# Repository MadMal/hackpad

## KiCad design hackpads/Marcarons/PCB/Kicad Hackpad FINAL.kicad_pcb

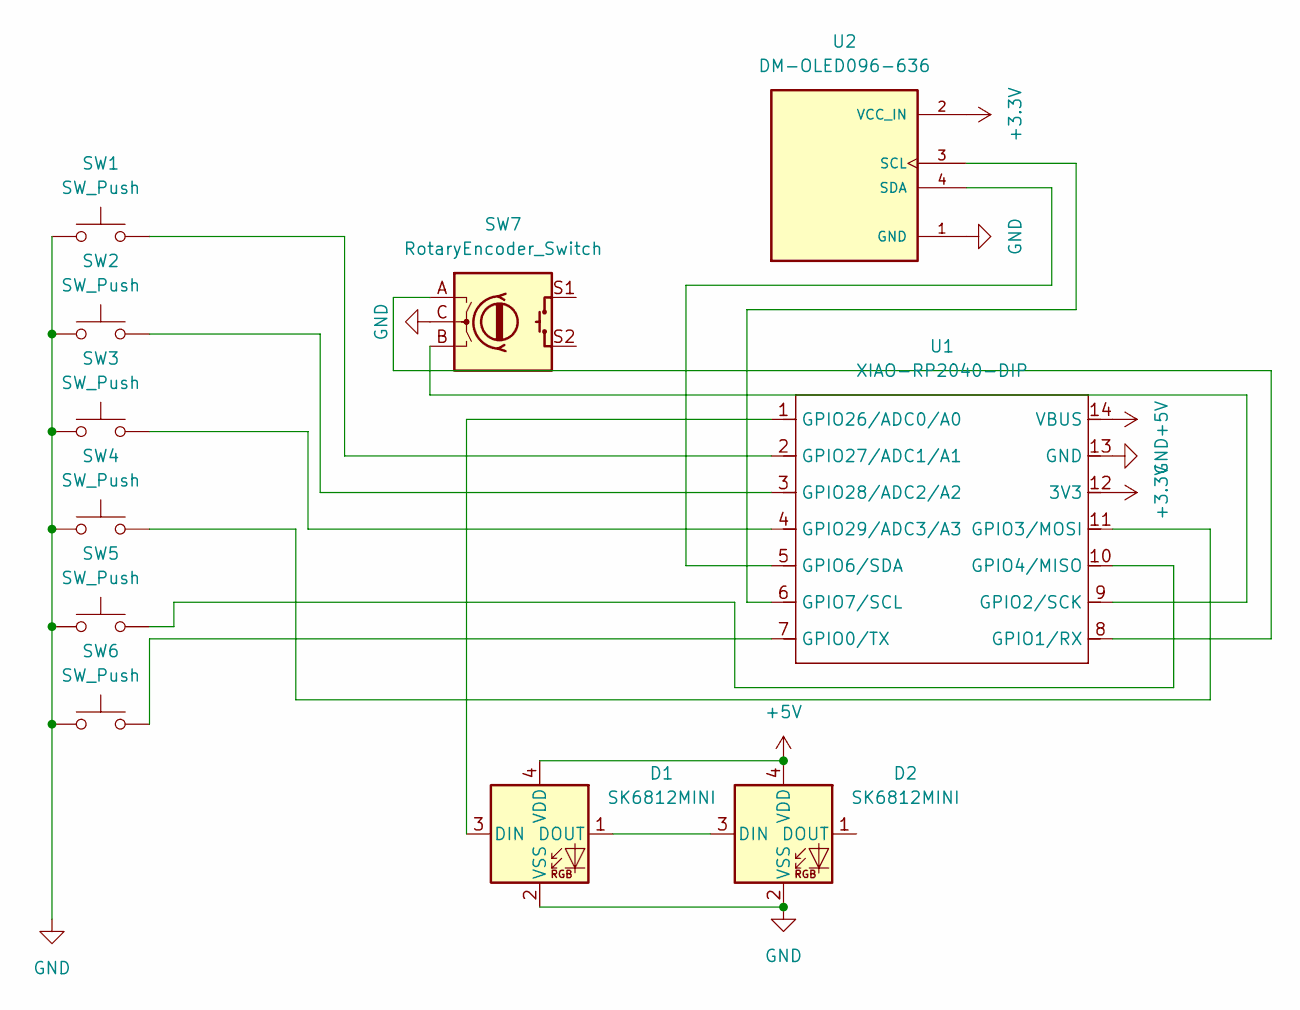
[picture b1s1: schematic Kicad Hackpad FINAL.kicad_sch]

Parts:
D1, D2: SK6812MINI; LED_SK6812MINI_PLCC4_3.5x3.5mm_P1.75mm
SW1, SW2, SW3, SW4, SW5, SW6: SW_Push; SW_Cherry_MX_1.00u_PCB
SW7: RotaryEncoder_Switch; RotaryEncoder_Alps_EC11E-Switch_Vertical_H20mm
U1: XIAO-RP2040-DIP
U2: DM-OLED096-636; SSD1306-0.91-OLED-4pin-128x32; PARTREV 2018-09-10

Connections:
+3.3V: U1.12 (3V3), U2.2 (VCC_IN)
+5V: D1.4 (VDD), D2.4 (VDD), U1.14 (VBUS)
GND: D1.2 (VSS), D2.2 (VSS), SW1.1, SW2.1, SW3.1, SW4.1, SW5.1, SW6.1, SW7.C, U1.13 (GND), U2.1 (GND)
unnamed: D1.3 (DIN), U1.1 (GPIO26/ADC0/A0)
unnamed: D1.1 (DOUT), D2.3 (DIN)
unnamed: SW6.2, U1.7 (GPIO0/TX)
unnamed: SW7.A, U1.8 (GPIO1/RX)
unnamed: SW7.B, U1.9 (GPIO2/SCK)
unnamed: SW4.2, U1.11 (GPIO3/MOSI)
unnamed: SW5.2, U1.10 (GPIO4/MISO)
unnamed: U1.5 (GPIO6/SDA), U2.4 (SDA)
unnamed: U1.6 (GPIO7/SCL), U2.3 (SCL)
unnamed: SW1.2, U1.2 (GPIO27/ADC1/A1)
unnamed: SW2.2, U1.3 (GPIO28/ADC2/A2)
unnamed: SW3.2, U1.4 (GPIO29/ADC3/A3)

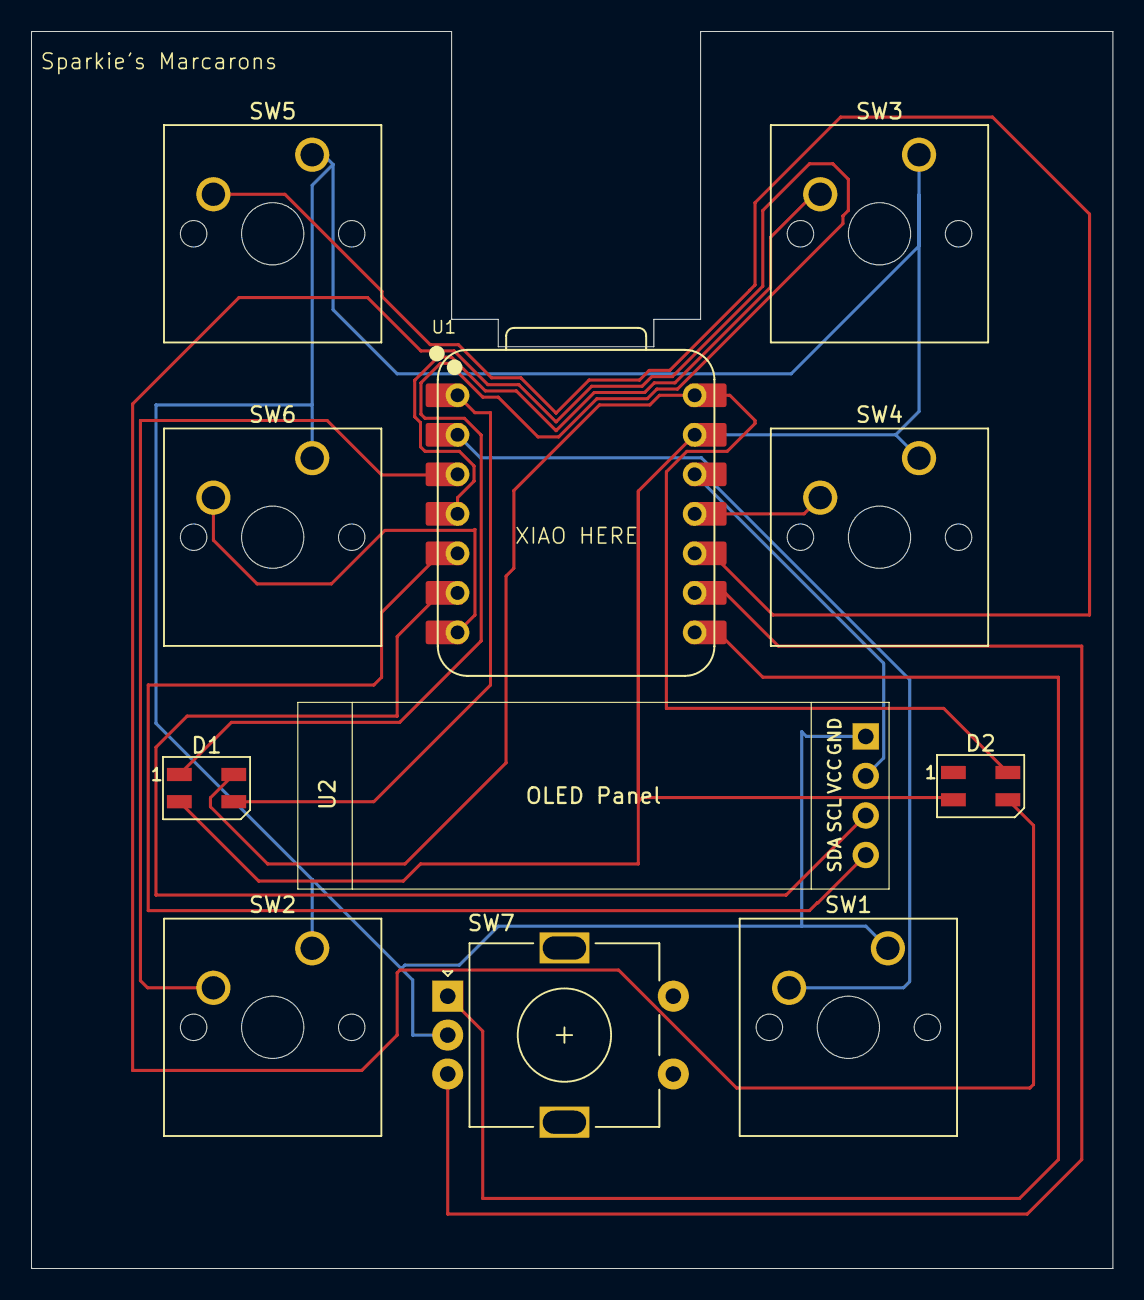
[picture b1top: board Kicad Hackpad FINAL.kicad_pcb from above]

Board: 2 copper layers, 69.5 x 79.5 mm, 11 parts (0 on the bottom side), 15 nets.
